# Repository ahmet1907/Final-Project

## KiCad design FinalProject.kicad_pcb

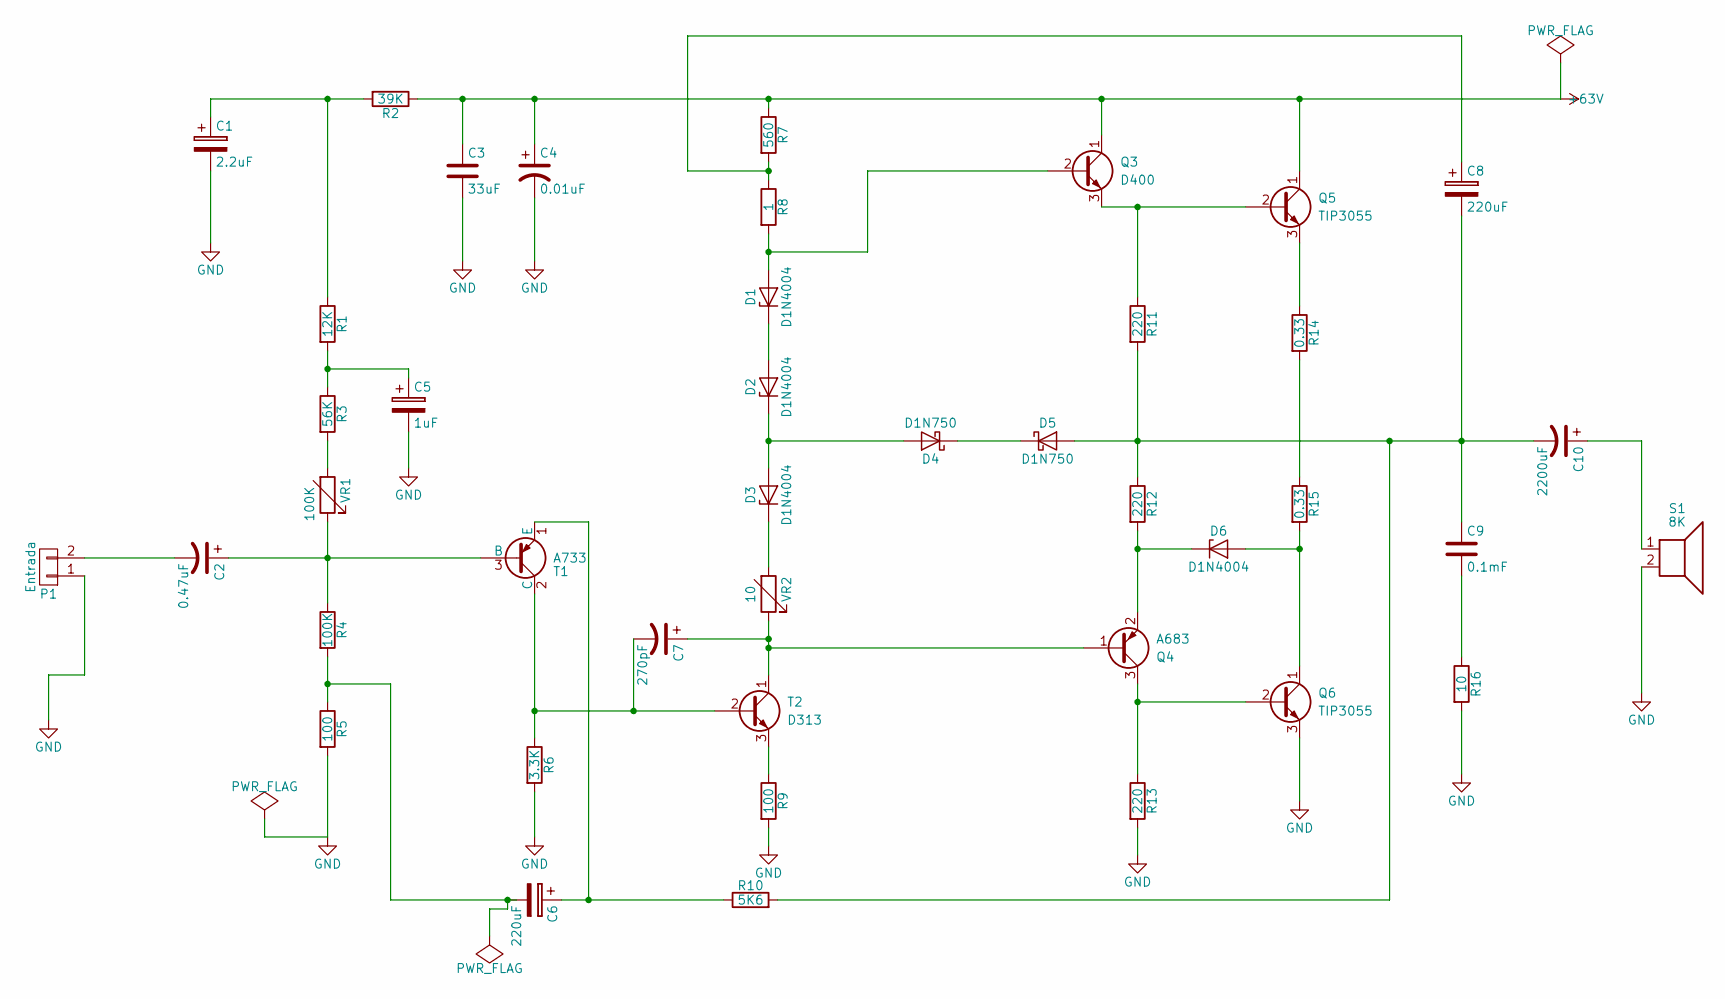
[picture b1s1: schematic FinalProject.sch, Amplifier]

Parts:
C1: 2.2uF; CP_Axial_L10.0mm_D4.5mm_P15.00mm_Horizontal
C2: 0.47uF; CP_Axial_L11.0mm_D5.0mm_P18.00mm_Horizontal
C3: 33uF; CP_Axial_L11.0mm_D5.0mm_P18.00mm_Horizontal
C4: 0.01uF; CP_Axial_L11.0mm_D5.0mm_P18.00mm_Horizontal
C5: 1uF; CP_Axial_L10.0mm_D4.5mm_P15.00mm_Horizontal
C6, C8: 220uF; CP_Axial_L10.0mm_D4.5mm_P15.00mm_Horizontal
C7: 270pF; CP_Axial_L10.0mm_D4.5mm_P15.00mm_Horizontal
C9: 0.1mF; CP_Axial_L10.0mm_D4.5mm_P15.00mm_Horizontal
C10: 2200uF; CP_Axial_L10.0mm_D4.5mm_P15.00mm_Horizontal
D1, D2, D3, D6: D1N4004; D_5W_P12.70mm_Horizontal
D4, D5: D1N750; D_5W_P12.70mm_Horizontal
P1: Entrada; RV_Disc_D12_W3.9_P7.5
Q3: D400; TO-92_Molded_Narrow
Q4: A683; TO-92_Molded_Narrow
Q5, Q6: TIP3055; TO-92_Molded_Narrow
R1: 12K; R_Axial_DIN0204_L3.6mm_D1.6mm_P7.62mm_Horizontal
R2: 39K; R_Axial_DIN0204_L3.6mm_D1.6mm_P7.62mm_Horizontal
R3: 56K; R_Axial_DIN0204_L3.6mm_D1.6mm_P7.62mm_Horizontal
R4: 100K; R_Axial_DIN0204_L3.6mm_D1.6mm_P7.62mm_Horizontal
R5, R9: 100; R_Axial_DIN0204_L3.6mm_D1.6mm_P7.62mm_Horizontal
R6: 3.3K; R_Axial_DIN0204_L3.6mm_D1.6mm_P7.62mm_Horizontal
R7: 560; R_Axial_DIN0204_L3.6mm_D1.6mm_P7.62mm_Horizontal
R8: 1; R_Axial_DIN0204_L3.6mm_D1.6mm_P7.62mm_Horizontal
R10: 5K6; R_Axial_DIN0204_L3.6mm_D1.6mm_P7.62mm_Horizontal
R11, R12, R13: 220; R_Axial_DIN0204_L3.6mm_D1.6mm_P7.62mm_Horizontal
R14, R15: 0.33; R_Axial_DIN0204_L3.6mm_D1.6mm_P7.62mm_Horizontal
R16: 10; R_Axial_DIN0204_L3.6mm_D1.6mm_P7.62mm_Horizontal
S1: 8K; RV_Disc_D12_W3.9_P7.5
T1: A733; TO-92_Molded_Narrow
T2: D313; TO-92_Molded_Narrow
VR1: 100K; Potentiometer_Piher_T16H_Single_Vertical
VR2: 10; Potentiometer_Piher_T16H_Single_Vertical

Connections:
+63V: C3.1, C4.1, Q3.1 (C), Q5.1 (C), R2.1, R7.1
GND: C1.2, C3.2, C4.2, C5.2, P1.1, Q6.3 (E), R5.2, R6.2, R9.2, R13.2, R16.2, S1.2
unnamed: C1.1, R1.1, R2.2
unnamed: C2.1, R4.1, T1.3 (B), VR1.1
unnamed: C2.2, P1.2
unnamed: C5.1, R1.2, R3.1
unnamed: C6.1, R10.1, T1.1 (E)
unnamed: C6.2, R4.2, R5.1
unnamed: C7.1, Q4.1 (B), T2.1 (C), VR2.1
unnamed: C7.2, R6.1, T1.2 (C), T2.2 (B)
unnamed: C8.1, R7.2, R8.1
unnamed: C9.2, R16.1
unnamed: C10.1, S1.1
unnamed: C8.2, C9.1, C10.2, D5.2 (A), R10.2, R11.2, R12.1
unnamed: D1.1 (K), D2.2 (A)
unnamed: D1.2 (A), Q3.2 (B), R8.2
unnamed: D2.1 (K), D3.2 (A), D4.2 (A)
unnamed: D3.1 (K), VR2.2
unnamed: D4.1 (K), D5.1 (K)
unnamed: D6.1 (K), Q4.2 (E), R12.2
unnamed: D6.2 (A), Q6.1 (C), R15.2
unnamed: Q3.3 (E), Q5.2 (B), R11.1
unnamed: Q4.3 (C), Q6.2 (B), R13.1
unnamed: Q5.3 (E), R14.1
unnamed: R3.2, VR1.2
unnamed: R9.1, T2.3 (E)
unnamed: R14.2, R15.1

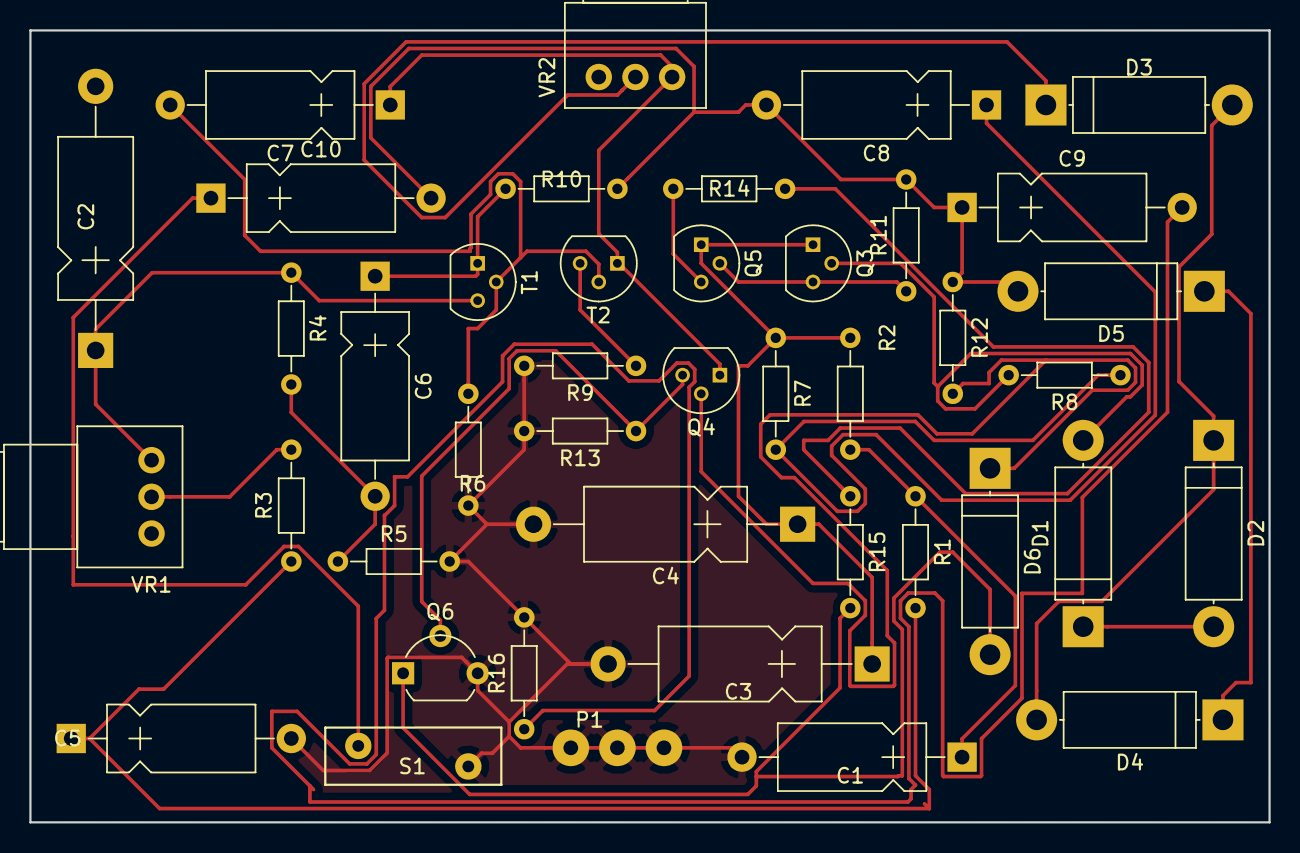
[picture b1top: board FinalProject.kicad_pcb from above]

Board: 2 copper layers, 84.5 x 54.0 mm, 42 parts (0 on the bottom side), 26 nets.

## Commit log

2017-06-13 Final Project
